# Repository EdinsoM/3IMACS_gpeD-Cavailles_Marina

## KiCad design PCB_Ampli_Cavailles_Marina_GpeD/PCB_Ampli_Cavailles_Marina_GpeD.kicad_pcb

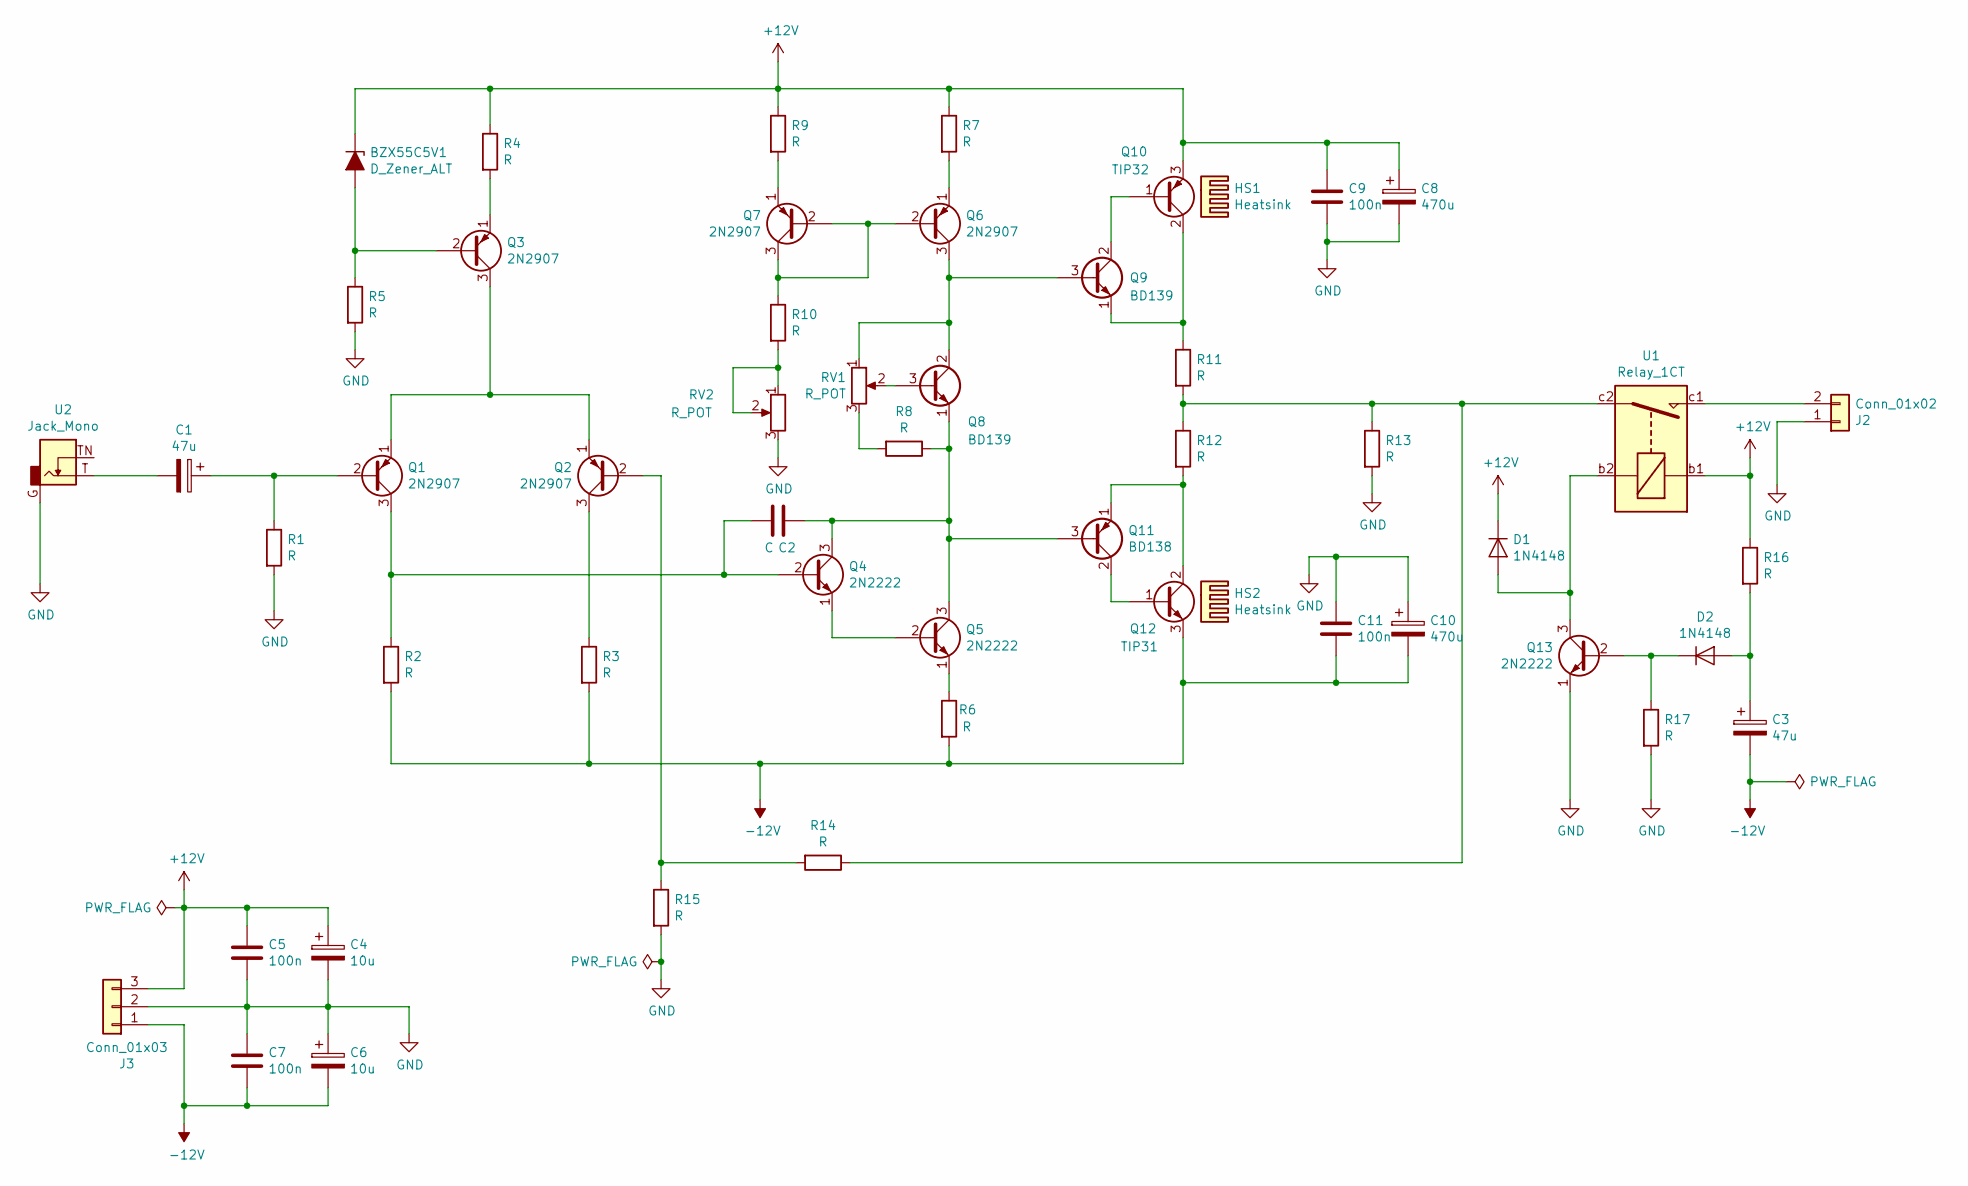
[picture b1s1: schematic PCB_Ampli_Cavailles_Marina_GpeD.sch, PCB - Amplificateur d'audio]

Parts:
BZX55C5V1: D_Zener_ALT; D_DO-35_SOD27_P10.16mm_Horizontal
C1, C3: 47u; CP_Radial_D8.0mm_P5.00mm
C2: C; C_Rect_L7.2mm_W3.5mm_P5.00mm_FKS2_FKP2_MKS2_MKP2
C4, C6: 10u; CP_Radial_D8.0mm_P5.00mm
C5, C7, C9, C11: 100n; C_Rect_L7.2mm_W3.5mm_P5.00mm_FKS2_FKP2_MKS2_MKP2
C8, C10: 470u; CP_Radial_D12.5mm_P5.00mm
D1, D2: 1N4148; D_DO-35_SOD27_P10.16mm_Horizontal
HS1, HS2: Heatsink; Heatsink_Fischer_SK104-STC-STIC_35x13mm_2xDrill2.5mm
J2: Conn_01x02; PhoenixContact_MSTBVA_2,5_2-G-5,08_1x02_P5.08mm_Vertical
J3: Conn_01x03; PhoenixContact_MSTBVA_2,5_3-G-5,08_1x03_P5.08mm_Vertical
Q1, Q2, Q3, Q6, Q7: 2N2907; TO-18-3
Q4, Q5, Q13: 2N2222; TO-18-3
Q8, Q9: BD139; TO-126-3_Vertical
Q10: TIP32; TO-220-3_Vertical
Q11: BD138; TO-126-3_Vertical
Q12: TIP31; TO-220-3_Vertical
R1, R2, R3, R4, R5, R6, R7, R8, R9, R10, R13, R14, R15, R16, R17: R; R_Axial_DIN0207_L6.3mm_D2.5mm_P10.16mm_Horizontal
R11, R12: R; R_Axial_DIN0516_L15.5mm_D5.0mm_P20.32mm_Horizontal
RV1, RV2: R_POT; Potentiometer_Bourns_3296W_Vertical
U1: Relay_1CT; Relais_112LMH2
U2: Jack_Mono; Jack_35RAPC2AV

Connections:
+12V: BZX55C5V1.1 (K), C4.1, C5.1, C8.1, C9.1, D1.1 (K), J3.3, Q10.3 (E), R4.1, R7.1, R9.1, R16.1, U1.b1
-12V: C3.2, C6.2, C7.2, C10.2, C11.2, J3.1, Q12.3 (E), R2.2, R3.2, R6.2
GND: C4.2, C5.2, C6.1, C7.1, C8.2, C9.2, C10.1, C11.1, J2.1, J3.2, Q13.1 (E), R1.2, R5.2, R13.2, R15.2, R17.2, RV2.3, U2.G
unnamed: BZX55C5V1.2 (A), Q3.2 (B), R5.1
unnamed: C1.1, Q1.2 (B), R1.1
unnamed: C1.2, U2.T
unnamed: C2.1, Q4.3 (C), Q5.3 (C), Q8.1 (E), Q11.3 (B), R8.1
unnamed: C2.2, Q1.3 (C), Q4.2 (B), R2.1
unnamed: C3.1, D2.2 (A), R16.2
unnamed: D1.2 (A), Q13.3 (C), U1.b2
unnamed: D2.1 (K), Q13.2 (B), R17.1
unnamed: J2.2, U1.c1
unnamed: Q1.1 (E), Q2.1 (E), Q3.3 (C)
unnamed: Q2.2 (B), R14.2, R15.1
unnamed: Q2.3 (C), R3.1
unnamed: Q3.1 (E), R4.2
unnamed: Q4.1 (E), Q5.2 (B)
unnamed: Q5.1 (E), R6.1
unnamed: Q6.1 (E), R7.2
unnamed: Q6.2 (B), Q7.2 (B), Q7.3 (C), R10.1
unnamed: Q6.3 (C), Q8.2 (C), Q9.3 (B), RV1.1
unnamed: Q7.1 (E), R9.2
unnamed: Q8.3 (B), RV1.2
unnamed: Q9.2 (C), Q10.1 (B)
unnamed: Q9.1 (E), Q10.2 (C), R11.1
unnamed: Q11.1 (E), Q12.2 (C), R12.2
unnamed: Q11.2 (C), Q12.1 (B)
unnamed: R8.2, RV1.3
unnamed: R10.2, RV2.1, RV2.2
unnamed: R11.2, R12.1, R13.1, R14.1, U1.c2

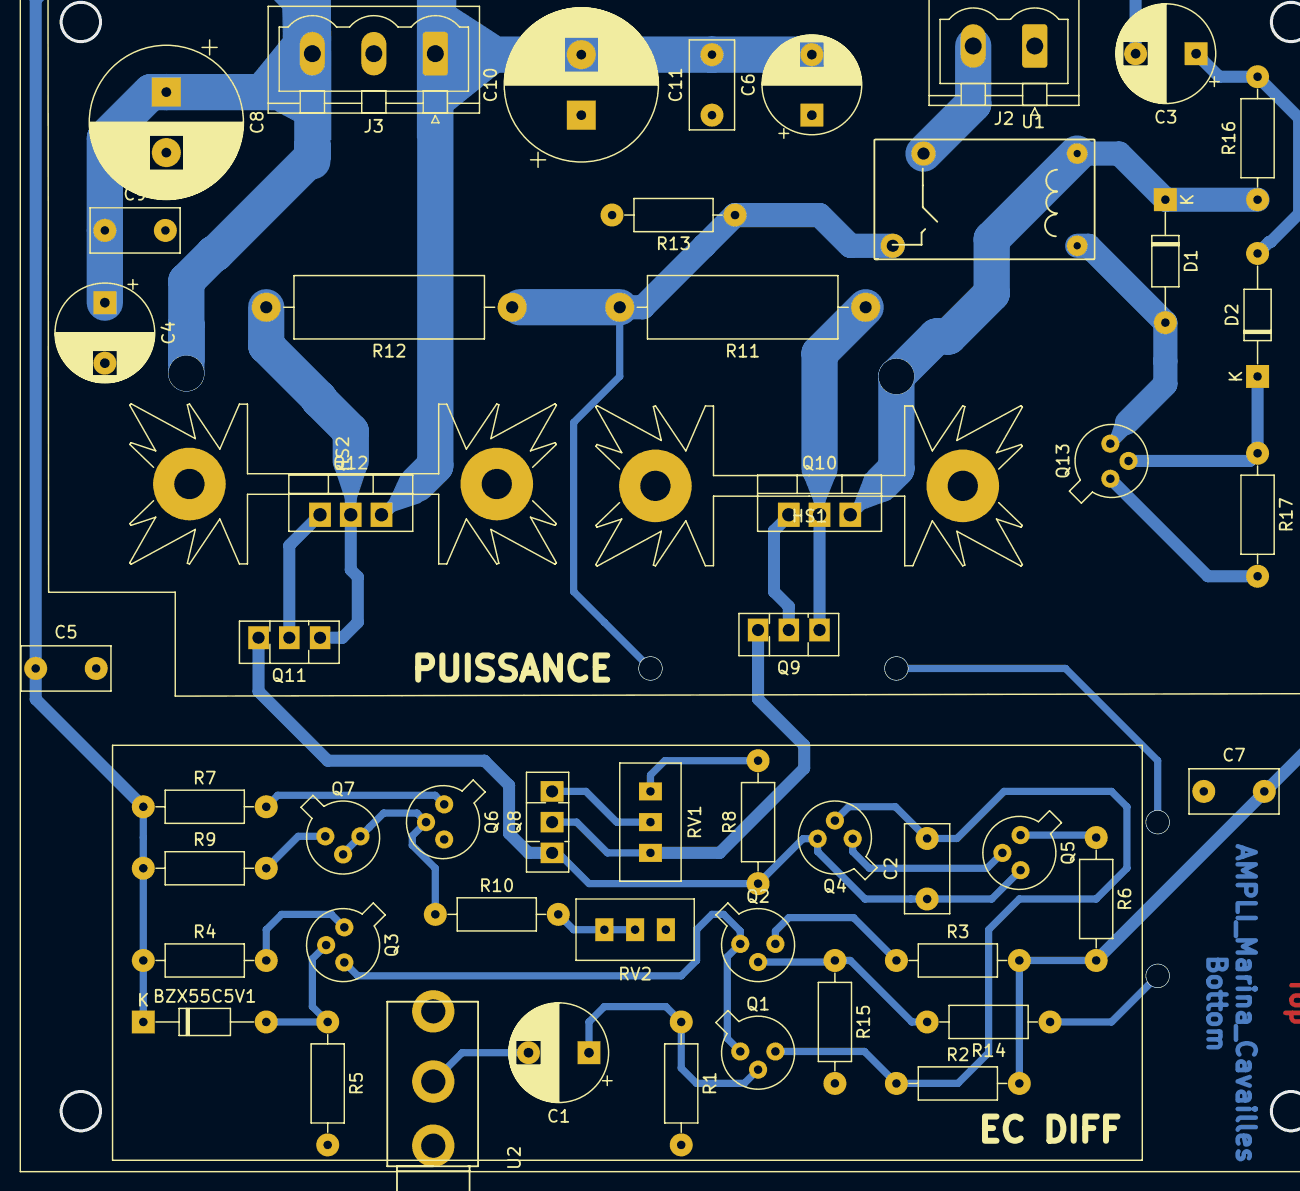
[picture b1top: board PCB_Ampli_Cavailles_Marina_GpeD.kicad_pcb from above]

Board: 2 copper layers, 52 parts (0 on the bottom side), 30 nets.

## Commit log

2020-03-23 Schema
2020-03-23 Jack_Mono ajouté
2020-03-23 Quelques changes
2020-03-24 Quelques élements associées aux footprints
2020-03-24 Nouvelles associations de footprints
2020-03-24 Petit changes
2020-04-08 PCB Modifié
2020-04-08 Il manque finir le routage
2020-04-09 Il manque 1 routage
2020-04-09 Routage fini
2020-04-12 New PCB
    On a separé les sections: puissance et diff, et on a mis en place differents Track Witdh
2020-04-12 4mm pour R13 à GND
2020-04-12 Cambiadas las orientaciones de las alimentaciones y la salida
2020-04-12 Cambio menor
2020-04-12 Cambios menores
2020-04-14 Nouvelle PCB
2020-04-16 Quatrième PCB (plaque de masse inclus)
2020-04-20 Straps en violet
2020-11-17 Revert "Delete PCB_Ampli_Cavailles_Marina_GpeD.rar"
    This reverts commit afc5043583de255b65c2f9ac1f3cfc6bfa49c47f.
